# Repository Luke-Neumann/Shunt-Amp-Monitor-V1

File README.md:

# Shunt-Amp-Monitor
Using a shunt to monitor large currents through a wire.
Board was designed with EAGLE.

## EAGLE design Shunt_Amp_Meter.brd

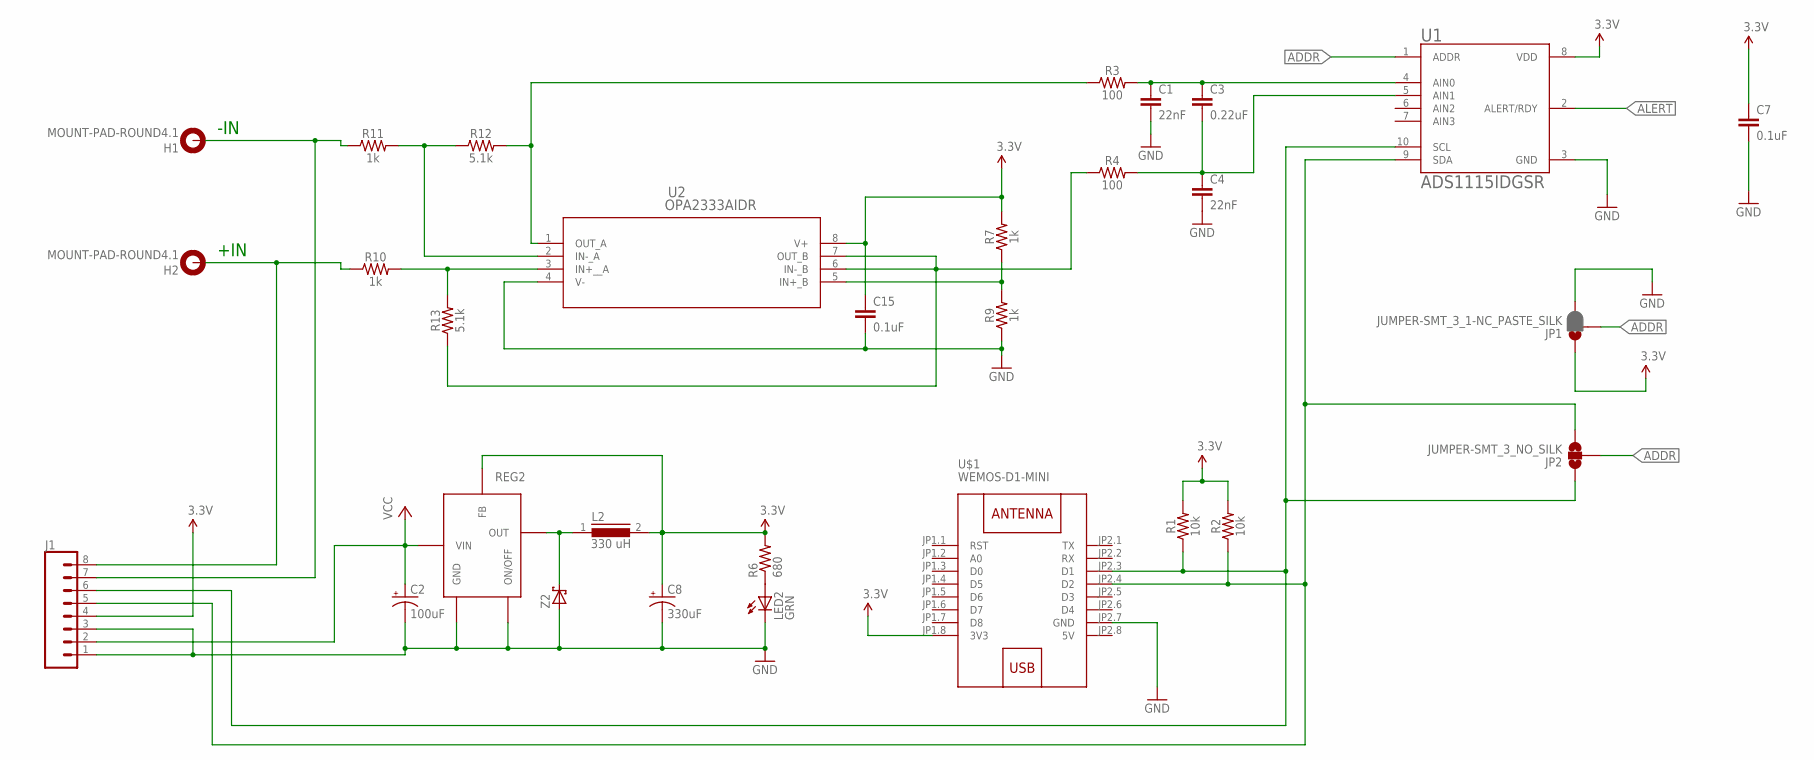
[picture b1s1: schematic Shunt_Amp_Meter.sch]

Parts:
C1, C4: 22nF; 0603
C2: 100uF; F_CAP; DIGIKEY# PCE3917CT-ND
C3: 0.22uF; 0603
C7, C15: 0.1uF; 0603
C8: 330uF; F_CAP; DIGIKEY# PCE3401CT-ND
H1, H2: MOUNT-PAD-ROUND4.1; 4,1-PAD
J1: CONN_08"; 1X08
JP1: JUMPER-SMT_3_1-NC_PASTE_SILK; SMT-JUMPER_3_1-NC_PASTE_SILK
JP2: JUMPER-SMT_3_NO_SILK; SMT-JUMPER_3_NO_SILK
L2: 330 uH; DR125; DIGIKEY# SRR1208-102KLCT-ND
LED2: GRN; 0603_LED
R1, R2: 10k; 0603
R3, R4: 100; 0603
R6: 680; 0603_RESISTOR; DIGIKEY# P680GCT-ND
R7, R9, R10, R11: 1k; 0603
R12, R13: 5.1k; 0603
REG2: TL2575; TO-263-6
U1: ADS1115IDGSR; SOP50P490X110-10N
U2: OPA2333AIDR; D8
U$1: WEMOS-D1-MINI
Z2: SCHOTTKY_DIODE; SMD_DIODE

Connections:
3.3V: C7.1, C8.+, C15.1, J1.4, JP1.1, L2.2, R1.2, R2.2, R6.2, R7.2, REG2.4 (FB), U1.8 (VDD), U2.8 (V+), U$1.JP1.8 (3V3)
5V: U$1.JP2.8 (5V)
ADDR: JP1.2, JP2.2, U1.1 (ADDR)
ALERT: U1.2 (ALERT/RDY)
GND: C1.2, C2.-, C4.2, C7.2, C8.-, C15.2, J1.1, J1.3, JP1.3, LED2.C, R9.1, REG2.3 (GND), REG2.5 (ON/OFF), U1.3 (GND), U2.4 (V-), U$1.JP2.7 (GND), Z2.A
unnamed: C1.1, C3.1, R3.2, U1.4 (AIN0)
unnamed: C3.2, C4.1, R4.2, U1.5 (AIN1)
unnamed: J1.6, JP2.1, R1.1, U1.10 (SCL), U$1.JP2.3 (D1)
unnamed: J1.5, JP2.3, R2.1, U1.9 (SDA), U$1.JP2.4 (D2)
unnamed: H1.B4,1, J1.7, R11.1
unnamed: H2.B4,1, J1.8, R10.1
unnamed: R7.1, R9.2, U2.5 (IN+_B)
unnamed: L2.1, REG2.2 (OUT), Z2.C
unnamed: LED2.A, R6.1
unnamed: R10.2, R13.2, U2.3 (IN+__A)
unnamed: R4.1, R13.1, U2.6 (IN-_B), U2.7 (OUT_B)
unnamed: R11.2, R12.1, U2.2 (IN-_A)
unnamed: R3.1, R12.2, U2.1 (OUT_A)
VCC: C2.+, J1.2, REG2.1 (VIN)

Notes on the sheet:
+IN
-IN

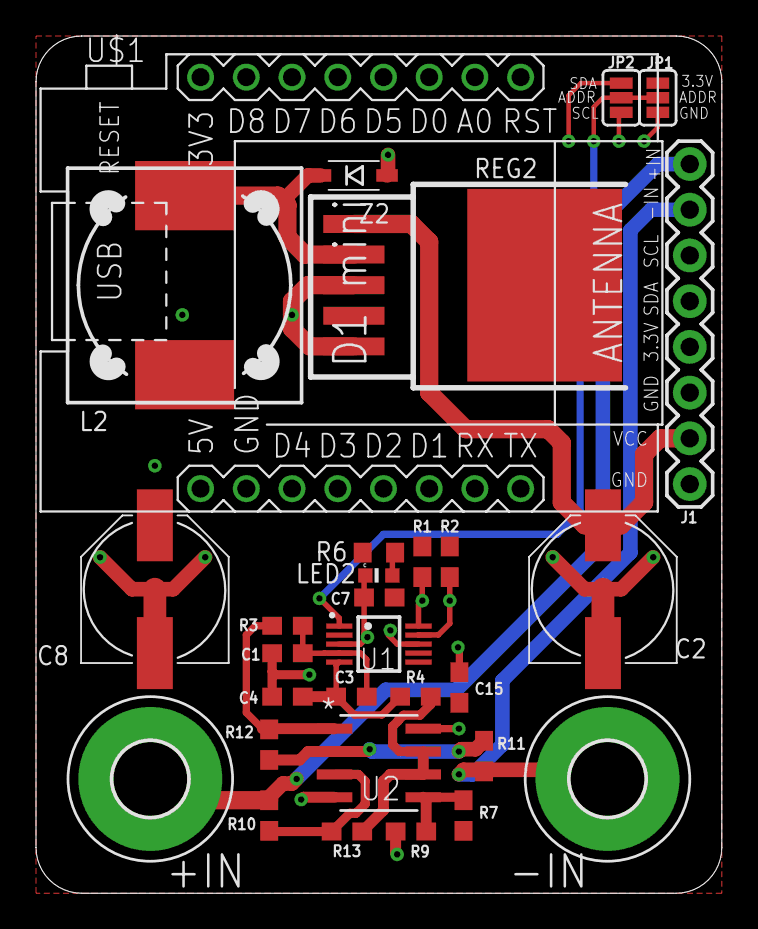
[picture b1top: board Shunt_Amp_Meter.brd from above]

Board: 4 copper layers, 38.1 x 47.6 mm, 30 parts (0 on the bottom side), 17 nets.

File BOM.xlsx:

Qty | Value | Parts | digi-key part # | Device | Package
1 |  | J1 | S7041-ND | CONN_08 - top layer
1 |  | Z2 | 641-1458-1-ND | SCHOTTKY_DIODE | SMD_DIODE
1 |  | REG2 | 296-21828-1-ND | TL2575 | TO-263-6
1 | 0.1uF | C15 | 1276-1000-1-ND | 0.1UF-0603-25V-(+80/-20%) | 603
1 | 0.1uF | C7 | 1276-1000-1-ND | 0.1UF-0603-25V-5% | 603
1 | 0.22uF | C3 | 399-7884-1-ND | 0.22UF-0603-25V-10% | 603
2 | 100 | R3, R4 | P100DBCT-ND | 100OHM-0603-1/4W-5% | 603
1 | 100uF | C2 | PCE3917CT-ND | CAP_POLF | F_CAP
2 | 10k | R1, R2 | 311-10KDCT-ND | 10KOHM-0603-1/10W-1% | 603
4 | 1k | R7, R9, R10, R11 | P1.0KBECT-ND | 1KOHM-0603-1/10W-1% | 603
2 | 22nF | C1, C4 | 399-9043-1-ND | 22NF/22,000PF-0603-50V-10% | 603
1 | 330 uH | L2 | SRR1208-331KLCT-ND | DR125 | DR125
1 | 330uF | C8 | PCE5018CT-ND | CAP_POLF | F_CAP
2 | 5.1k | R12, R13 | P5.1KBECT-ND | RESISTOR0603 | 603
1 | 680 | R6 | P680GCT-ND | RESISTOR0603 | 0603_RESISTOR
1 | ADS1115IDGSR | U1 | 296-38849-1-ND | ADS1115IDGSR | SOP50P490X110-10N
1 | GRN | LED2 | 516-2493-1-ND | LED0603 | 0603_LED
1 | OPA2333AIDR | U2 | 296-26249-1-ND | OPA2333AIDR | D8
1 | WEMOS-D1-MINI | U$1 | S7041-ND | Use two female CONN-08 top layer | WEMOS-D1-MINI

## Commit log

2019-06-25 Create Hardware

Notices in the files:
parts and their libraries:
SparkFun-Capacitors: Licensing: Creative Commons ShareAlike 4.0 International - https://creativecommons.org/licenses/by-sa/4.0
diy-modules: Released under the Creative Commons Attribution 4.0 International License: http://creativecommons.org/licenses/by/4.0
